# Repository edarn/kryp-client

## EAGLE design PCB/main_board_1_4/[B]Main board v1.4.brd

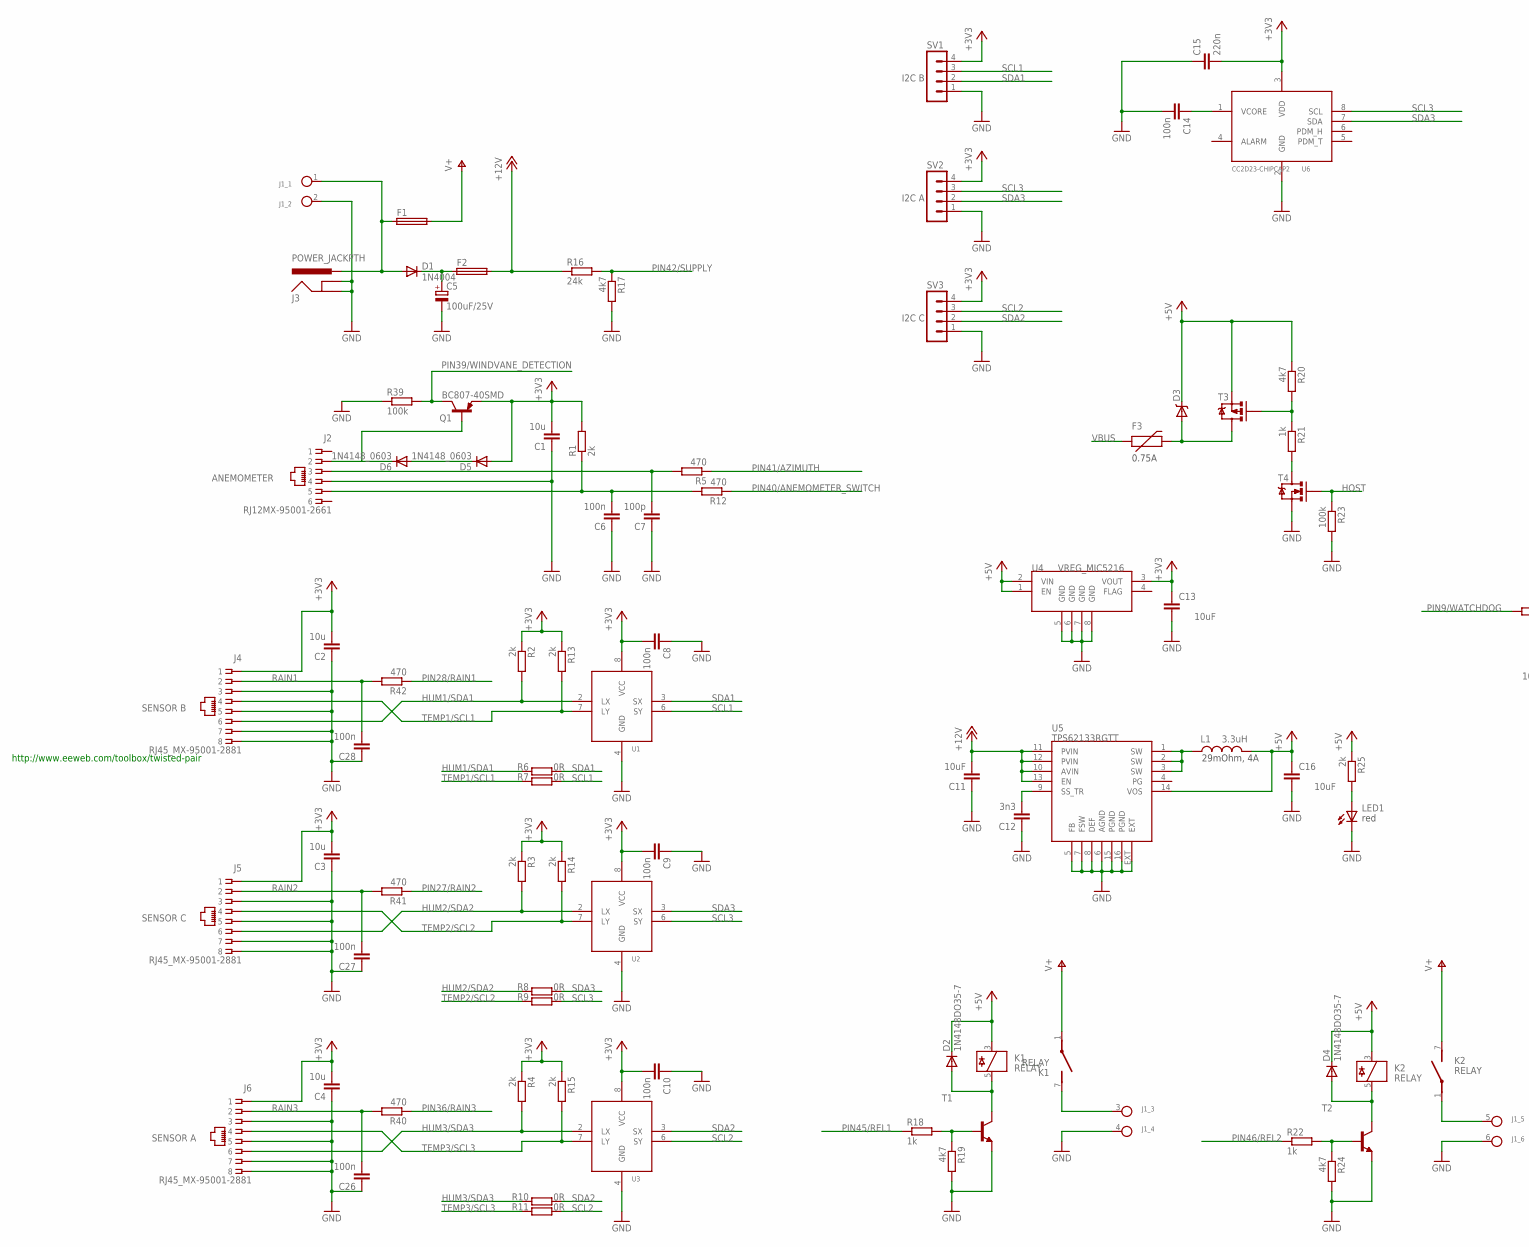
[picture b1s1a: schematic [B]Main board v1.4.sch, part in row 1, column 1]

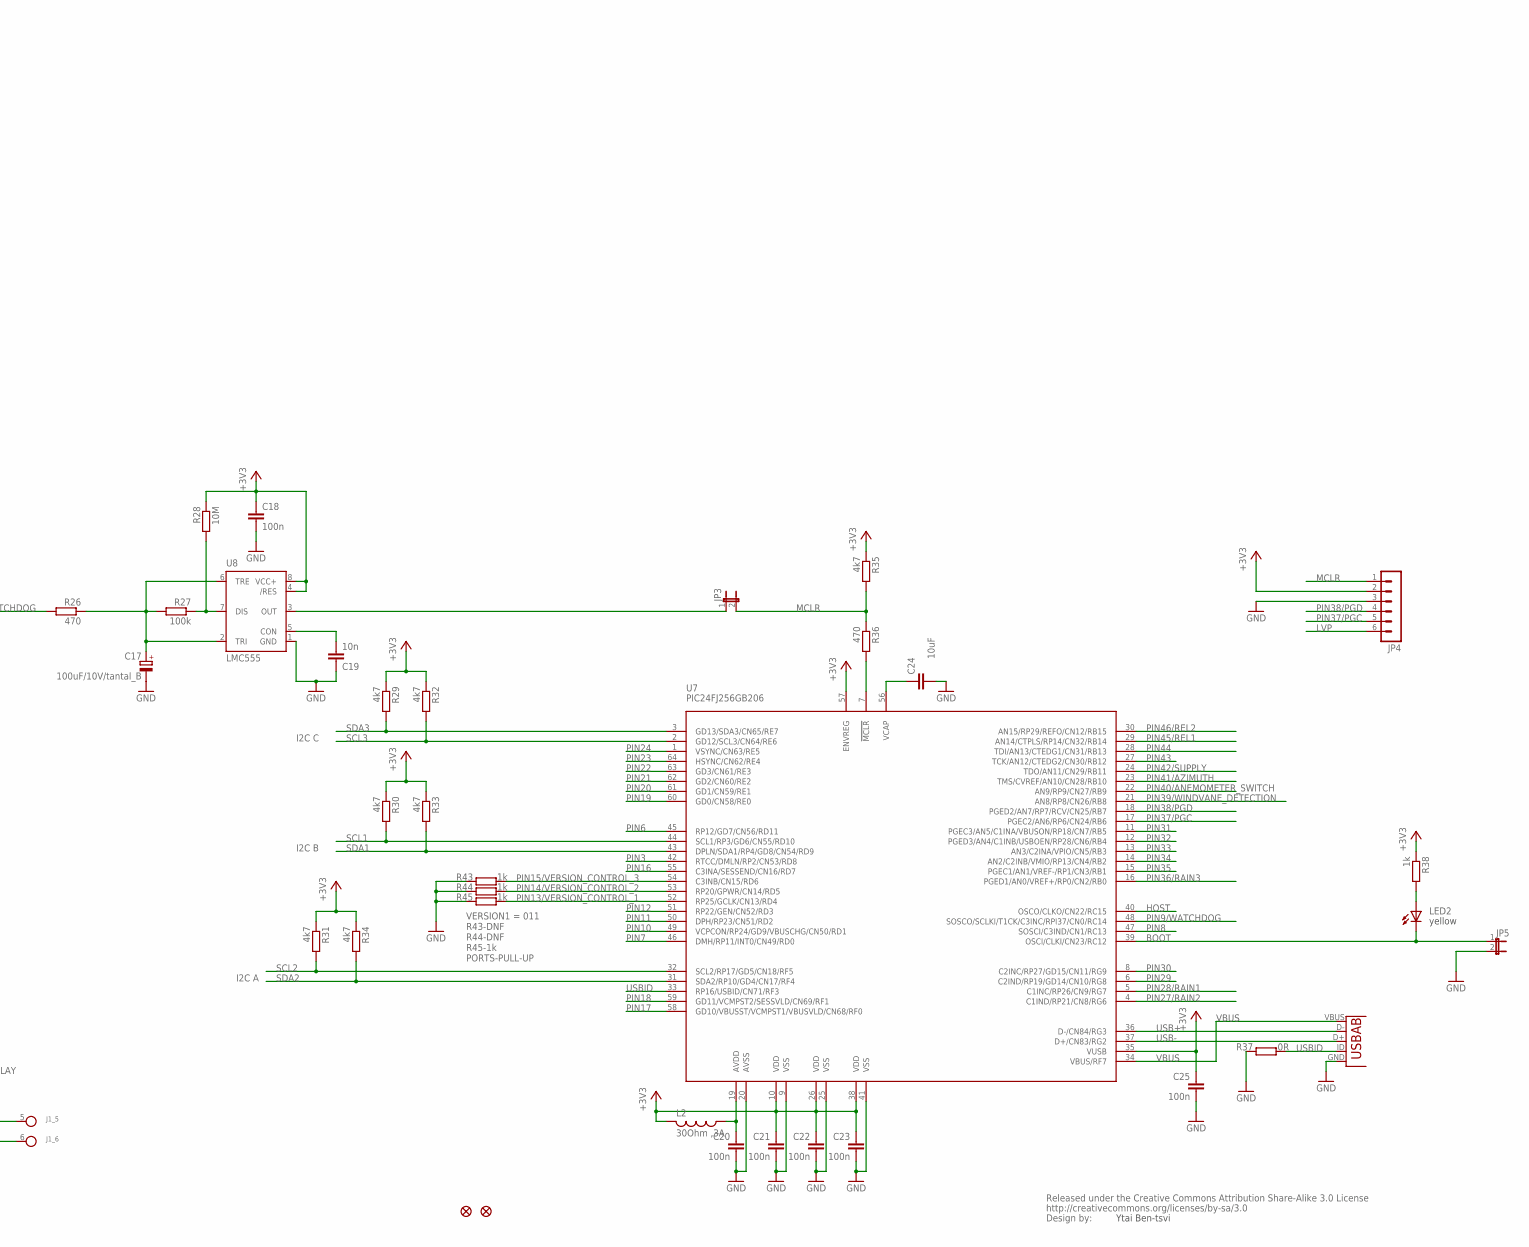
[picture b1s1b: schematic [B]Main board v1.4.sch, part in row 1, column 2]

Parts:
C1, C2, C3, C4: 10u; C1206
C5: 100uF/25V; E2-5
C6, C8, C9, C10, C14, C18, C20, C21, C22, C23, C25, C26, C27, C28: 100n; C1206
C7: 100p; C1206
C11, C13, C16, C24: 10uF; C1206
C12: 3n3; C1206
C15: 220n; C1206
C17: 100uF/10V/tantal_B; B/3528-21R
C19: 10n; C1206
D1: 1N4004; DO41-10
D2, D4: 1N4148DO35-7; DO35-7
D3: B340A; SMA-DIODE; PART# B340A
D5, D6: 1N4148_0603; D0603
F1, F2: FUSE_HOLDER; ZHL30
F3: PTCSMD; PTC-1206; PART# 0ZCA0075FF2G
J1: 6P_CONN; MOLEX_39543-0006
J2: RJ12MX-95001-2661; MX-95001-2661
J3: POWER_JACKPTH; PC-GK2.1
J4, J5, J6: RJ45_MX-95001-2881; MX-95001-2881
J7: 10104111-0001LF; USB-AB-MICRO-SMD
JP1, JP2: FIDUCIALUFIDUCIAL; MICRO-FIDUCIAL
JP3, JP5: JUMPER-2PTH; 1X02
JP4: MA06-1
K1, K2: RELAY; JV-5S-KT
L1: VLC5045T-3R3N; CR54
L2: 30Ohm ,3A; R1206
LED1: LS L29K-G1J2-1-Z; LED-1206
LED2: LY L29K-J1K2-26-Z; LED-1206
Q1: BC807-40SMD; SOT23-BEC
R1, R2, R3, R4, R13, R14, R15, R25: 2k; R1206
R5, R12, R26, R36, R40, R41, R42: 470; R1206
R6, R7, R8, R9, R10, R11, R37: 0R; R1206
R16: 24k; R1206
R17, R19, R20, R24, R29, R30, R31, R32, R33, R34, R35: 4k7; R1206
R18, R21, R22, R38, R43, R44, R45: 1k; R1206
R23, R27, R39: 100k; R1206
R28: 10M; R1206
SV1, SV2, SV3: MA04-1
T1, T2: BC817-16-NPN-SOT23-BEC; SOT23-BEC
T3: IRLML2244; SOT23-3
T4: 2N7002PW; SOT323; PART# 2N7002PW
U1, U2, U3: P82B715_I2C_BUS_EXTENDER; SO-08
U4: VREG_MIC5216; MSOP8
U5: TPS62133RGTT; QFN16-3X3MM
U6: CC2D23-CHIPCAP2
U7: PIC24FJ256GB206; PIC24FXXX_TQFP64
U8: LMC555; SO08
U$1: CREATIVE_COMMONS

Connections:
+3V3: C1.2, C2.2, C3.2, C4.2, C8.2, C9.2, C10.2, C13.2, C15.2, C18.1, C21.1, C22.1, C23.1, C25.1, D5.A, J4.1, J5.1, J6.1, JP4.2, L2.2, Q1.E, R1.2, R2.1, R3.1, R4.1, R13.1, R14.1, R15.1, R28.1, R29.1, R30.1, R31.1, R32.1, R33.1, R34.1, R35.1, R38.1, SV1.4, SV2.4, SV3.4, U1.8 (VCC), U2.8 (VCC), U3.8 (VCC), U4.3 (VOUT), U6.3 (VDD), U7.10 (VDD), U7.26 (VDD), U7.35 (VUSB), U7.38 (VDD), U7.57 (ENVREG), U8.4 (/RES), U8.8 (VCC+)
+5V: C16.2, D2.C, D3.C, D4.C, K1.3, K2.3, L1.P$2 (2), R20.1, R25.1, T3.2 (S), U4.1 (EN), U4.2 (VIN), U5.14 (VOS)
+12V: C11.2, F2.2, R16.1, U5.10 (AVIN), U5.11 (PVIN), U5.12 (PVIN), U5.13 (EN)
BOOT: JP5.1, LED2.C, U7.39 (OSCI/CLKI/CN23/RC12)
GND: C1.1, C2.1, C3.1, C4.1, C5.-, C6.1, C7.1, C8.1, C9.1, C10.1, C11.1, C12.1, C13.1, C14.2, C15.1, C16.1, C17.-, C18.2, C19.1, C20.2, C21.2, C22.2, C23.2, C24.1, C25.2, C26.1, C27.1, C28.1, J1.2, J1.4, J1.6, J2.4, J3.GND, J3.GNDBREAK, J4.3, J4.5, J4.7, J4.8, J5.3, J5.5, J5.7, J5.8, J6.3, J6.5, J6.7, J6.8, J7.GND, JP4.3, JP5.2, LED1.C, R17.2, R19.2, R23.2, R24.2, R37.2, R39.1, R43.1, R44.1, R45.1, SV1.1, SV2.1, SV3.1, T1.E, T2.E, T4.2 (S), U1.4 (GND), U2.4 (GND), U3.4 (GND), U4.5 (GND), U4.6 (GND), U4.7 (GND), U4.8 (GND), U5.5 (FB), U5.6 (AGND), U5.7 (FSW), U5.8 (DEF), U5.15 (PGND), U5.16 (PGND), U5.EXT, U6.2 (GND), U7.9 (VSS), U7.20 (AVSS), U7.25 (VSS), U7.41 (VSS), U8.1 (GND)
HOST: R23.1, T4.1 (G), U7.40 (OSCO/CLKO/CN22/RC15)
HUM1/SDA1: J4.6, R2.2, R6.2, U1.2 (LX)
HUM2/SDA2: J5.6, R3.2, R8.2, U2.2 (LX)
HUM3/SDA3: J6.6, R4.2, R10.2, U3.2 (LX)
LVP: JP4.6
MCLR: JP3.2, JP4.1, R35.2, R36.1
unnamed: D1.A, F1.1, J1.1, J3.PWR
unnamed: C6.2, J2.5, R1.1, R12.2
unnamed: C5.+, D1.C, F2.1
unnamed: C7.2, J2.3, R5.2
unnamed: C14.1, U6.1 (VCORE)
unnamed: R36.2, U7.7 (!MCLR)
unnamed: JP3.1, U8.3 (OUT)
unnamed: R18.2, R19.1, T1.B
unnamed: D2.A, K1.5, T1.C
unnamed: C19.2, U8.5 (CON)
unnamed: D6.C, J2.2, Q1.B
unnamed: J1.3, K1.7 (S)
unnamed: C17.+, R26.1, R27.2, U8.2 (TRI), U8.6 (TRE)
unnamed: D5.C, D6.A
unnamed: R27.1, R28.2, U8.7 (DIS)
unnamed: R22.2, R24.1, T2.B
unnamed: D4.A, K2.5, T2.C
unnamed: C24.2, U7.56 (VCAP)
unnamed: J1.5, K2.1
unnamed: LED2.A, R38.2
unnamed: LED1.A, R25.2
unnamed: D3.A, F3.2, T3.3 (D)
unnamed: C12.2, U5.9 (SS_TR)
unnamed: L1.P$1 (1), U5.1 (SW), U5.2 (SW), U5.3 (SW)
unnamed: C20.1, L2.1, U7.19 (AVDD)
unnamed: R20.2, R21.1, T3.1 (G)
unnamed: R21.2, T4.3 (D)
PIN3: U7.42 (RTCC/DMLN/RP2/CN53/RD8)
PIN6: U7.45 (RP12/GD7/CN56/RD11)
PIN7: U7.46 (DMH/RP11/INT0/CN49/RD0)
PIN8: U7.47 (SOSCI/C3IND/CN1/RC13)
PIN9/WATCHDOG: R26.2, U7.48 (SOSCO/SCLKI/T1CK/C3INC/RPI37/CN0/RC14)
PIN10: U7.49 (VCPCON/RP24/GD9/VBUSCHG/CN50/RD1)
PIN11: U7.50 (DPH/RP23/CN51/RD2)
PIN12: U7.51 (RP22/GEN/CN52/RD3)
PIN13/VERSION_CONTROL_1: R45.2, U7.52 (RP25/GCLK/CN13/RD4)
PIN14/VERSION_CONTROL_2: R44.2, U7.53 (RP20/GPWR/CN14/RD5)
PIN15/VERSION_CONTROL_3: R43.2, U7.54 (C3INB/CN15/RD6)
PIN16: U7.55 (C3INA/SESSEND/CN16/RD7)
PIN17: U7.58 (GD10/VBUSST/VCMPST1/VBUSVLD/CN68/RF0)
PIN18: U7.59 (GD11/VCMPST2/SESSVLD/CN69/RF1)
PIN19: U7.60 (GD0/CN58/RE0)
PIN20: U7.61 (GD1/CN59/RE1)
PIN21: U7.62 (GD2/CN60/RE2)
PIN22: U7.63 (GD3/CN61/RE3)
PIN23: U7.64 (HSYNC/CN62/RE4)
PIN24: U7.1 (VSYNC/CN63/RE5)
PIN27/RAIN2: R41.1, U7.4 (C1IND/RP21/CN8/RG6)
PIN28/RAIN1: R42.1, U7.5 (C1INC/RP26/CN9/RG7)
PIN29: U7.6 (C2IND/RP19/GD14/CN10/RG8)
PIN30: U7.8 (C2INC/RP27/GD15/CN11/RG9)
PIN31: U7.11 (PGEC3/AN5/C1INA/VBUSON/RP18/CN7/RB5)
PIN32: U7.12 (PGED3/AN4/C1INB/USBOEN/RP28/CN6/RB4)
PIN33: U7.13 (AN3/C2INA/VPIO/CN5/RB3)
PIN34: U7.14 (AN2/C2INB/VMIO/RP13/CN4/RB2)
PIN35: U7.15 (PGEC1/AN1/VREF-/RP1/CN3/RB1)
PIN36/RAIN3: R40.1, U7.16 (PGED1/AN0/VREF+/RP0/CN2/RB0)
PIN37/PGC: JP4.5, U7.17 (PGEC2/AN6/RP6/CN24/RB6)
PIN38/PGD: JP4.4, U7.18 (PGED2/AN7/RP7/RCV/CN25/RB7)
PIN39/WINDVANE_DETECTION: Q1.C, R39.2, U7.21 (AN8/RP8/CN26/RB8)
PIN40/ANEMOMETER_SWITCH: R12.1, U7.22 (AN9/RP9/CN27/RB9)
PIN41/AZIMUTH: R5.1, U7.23 (TMS/CVREF/AN10/CN28/RB10)
PIN42/SUPPLY: R16.2, R17.1, U7.24 (TDO/AN11/CN29/RB11)
PIN43: U7.27 (TCK/AN12/CTEDG2/CN30/RB12)
PIN44: U7.28 (TDI/AN13/CTEDG1/CN31/RB13)
PIN45/REL1: R18.1, U7.29 (AN14/CTPLS/RP14/CN32/RB14)
PIN46/REL2: R22.1, U7.30 (AN15/RP29/REFO/CN12/RB15)
RAIN1: C28.2, J4.2, R42.2
RAIN2: C27.2, J5.2, R41.2
RAIN3: C26.2, J6.2, R40.2
SCL1: R7.1, R30.2, SV1.3, U1.6 (SY), U7.44 (SCL1/RP3/GD6/CN55/RD10)
SCL2: R11.1, R31.2, SV3.3, U3.6 (SY), U7.32 (SCL2/RP17/GD5/CN18/RF5)
SCL3: R9.1, R32.2, SV2.3, U2.6 (SY), U6.8 (SCL), U7.2 (GD12/SCL3/CN64/RE6)
SDA1: R6.1, R33.2, SV1.2, U1.3 (SX), U7.43 (DPLN/SDA1/RP4/GD8/CN54/RD9)
SDA2: R10.1, R34.2, SV3.2, U3.3 (SX), U7.31 (SDA2/RP10/GD4/CN17/RF4)
SDA3: R8.1, R29.2, SV2.2, U2.3 (SX), U6.7 (SDA), U7.3 (GD13/SDA3/CN65/RE7)
TEMP1/SCL1: J4.4, R7.2, R13.2, U1.7 (LY)
TEMP2/SCL2: J5.4, R9.2, R14.2, U2.7 (LY)
TEMP3/SCL3: J6.4, R11.2, R15.2, U3.7 (LY)
USB+: J7.D-, U7.36 (D-/CN84/RG3)
USB-: J7.D+, U7.37 (D+/CN83/RG2)
USBID: J7.ID (USBID), R37.1, U7.33 (RP16/USBID/CN71/RF3)
V+: F1.2, K1.1, K2.7 (S)
VBUS: F3.1, J7.VBUS, U7.34 (VBUS/RF7)

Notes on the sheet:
http://www.eeweb.com/toolbox/twisted-pair
ANEMOMETER
SENSOR B
SENSOR A
SENSOR C
I2C C
I2C A
I2C B
Ytai Ben-tsvi
yellow
red
0.75A
29mOhm, 4A
VERSION1 = 011 R43-DNF R44-DNF R45-1k PORTS-PULL-UP

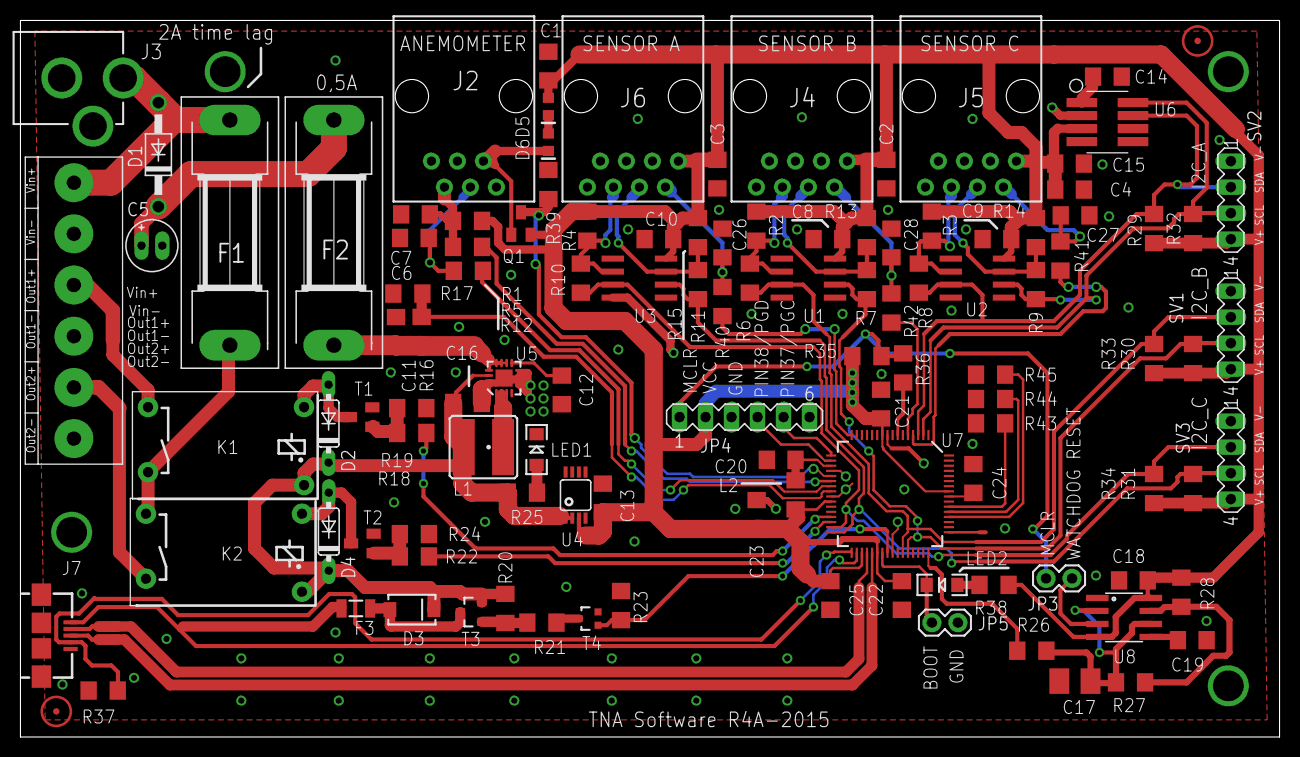
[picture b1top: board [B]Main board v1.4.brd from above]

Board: 2 copper layers, 123.0 x 70.0 mm, 117 parts (0 on the bottom side), 69 nets.

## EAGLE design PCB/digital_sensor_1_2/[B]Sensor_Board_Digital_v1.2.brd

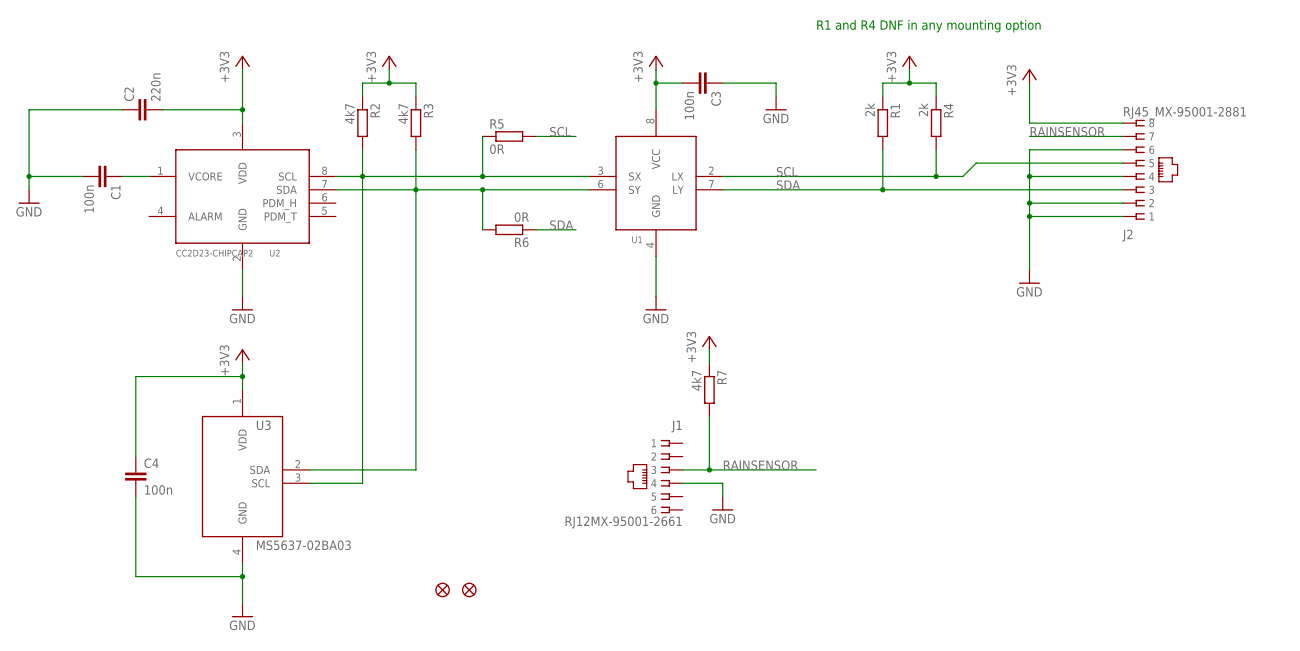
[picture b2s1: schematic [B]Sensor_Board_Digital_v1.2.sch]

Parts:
C1, C3, C4: 100n; C1206
C2: 220n; C1206
J1: RJ12MX-95001-2661; MX-95001-2661
J2: RJ45_MX-95001-2881; MX-95001-2881
JP1, JP2: FIDUCIALUFIDUCIAL; MICRO-FIDUCIAL
R1, R4: 2k; R1206
R2, R3, R7: 4k7; R1206
R5, R6: 0R; R1206
U1: P82B715_I2C_BUS_EXTENDER; SO-08
U2: CC2D23-CHIPCAP2
U3: MS5637-02BA03

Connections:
+3V3: C2.2, C3.2, C4.1, J2.8, R1.1, R2.1, R3.1, R4.1, R7.1, U1.8 (VCC), U2.3 (VDD), U3.1 (VDD)
GND: C1.2, C2.1, C3.1, C4.2, J1.4, J2.1, J2.2, J2.4, J2.6, U1.4 (GND), U2.2 (GND), U3.4 (GND)
unnamed: C1.1, U2.1 (VCORE)
unnamed: R2.2, R5.1, U1.3 (SX), U2.8 (SCL), U3.3 (SCL)
unnamed: R3.2, R6.2, U1.6 (SY), U2.7 (SDA), U3.2 (SDA)
RAINSENSOR: J1.3, J2.7, R7.2
SCL: J2.5, R4.2, R5.2, U1.2 (LX)
SDA: J2.3, R1.2, R6.1, U1.7 (LY)

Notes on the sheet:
R1 and R4 DNF in any mounting option

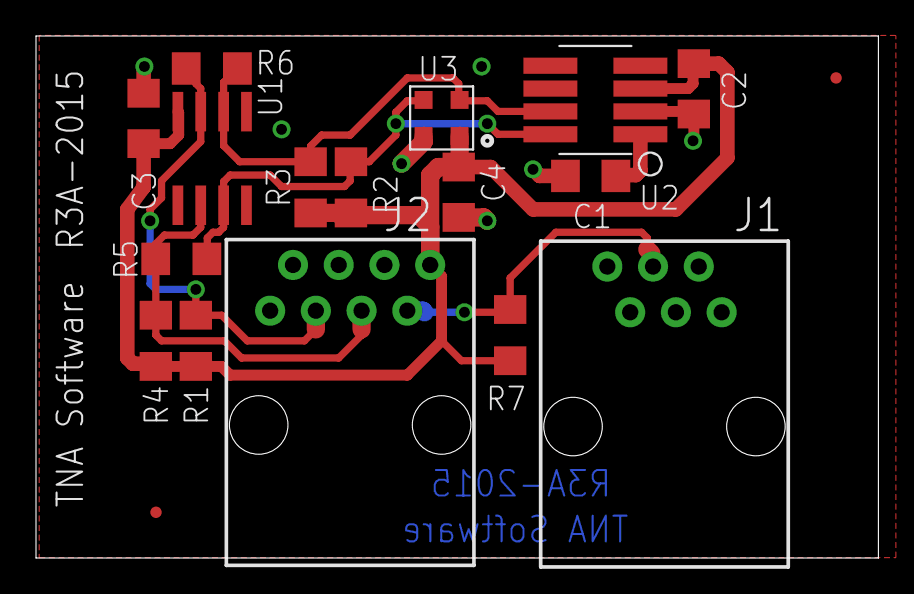
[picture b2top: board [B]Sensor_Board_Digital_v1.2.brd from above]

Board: 2 copper layers, 46.8 x 29.0 mm, 18 parts (0 on the bottom side), 8 nets.

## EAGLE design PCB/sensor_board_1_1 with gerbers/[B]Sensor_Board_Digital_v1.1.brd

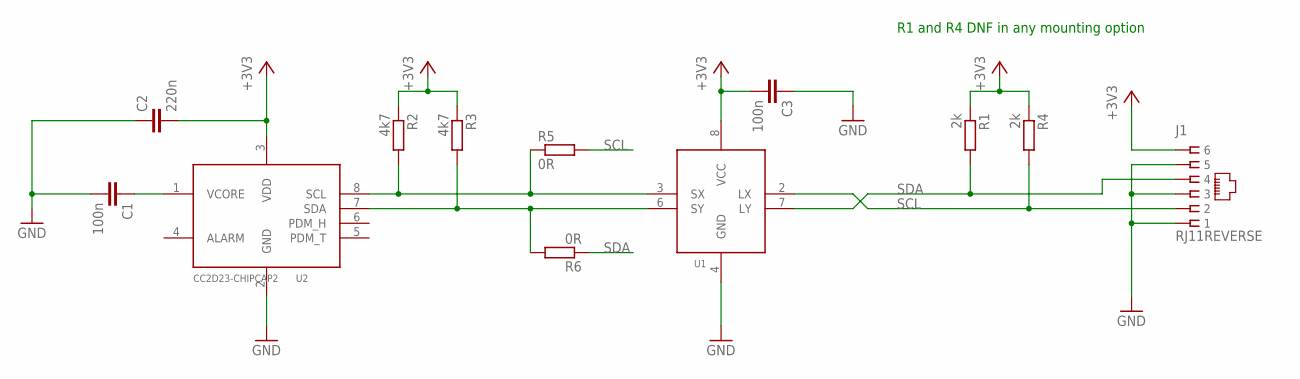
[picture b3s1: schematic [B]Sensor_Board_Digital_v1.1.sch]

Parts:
C1, C3: 100n; C1206
C2: 220n; C1206
J1: RJ11REVERSE; MX-95001-2661
R1, R4: 2k; R1206
R2, R3: 4k7; R1206
R5, R6: 0R; R1206
U1: P82B715_I2C_BUS_EXTENDER; SO-08
U2: CC2D23-CHIPCAP2

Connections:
+3V3: C2.2, C3.2, J1.6, R1.1, R2.1, R3.1, R4.1, U1.8 (VCC), U2.3 (VDD)
GND: C1.2, C2.1, C3.1, J1.1, J1.3, J1.5, U1.4 (GND), U2.2 (GND)
unnamed: C1.1, U2.1 (VCORE)
unnamed: R2.2, R5.1, U1.3 (SX), U2.8 (SCL)
unnamed: R3.2, R6.2, U1.6 (SY), U2.7 (SDA)
SCL: J1.2, R4.2, R5.2, U1.2 (LX)
SDA: J1.4, R1.2, R6.1, U1.7 (LY)

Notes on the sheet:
R1 and R4 DNF in any mounting option

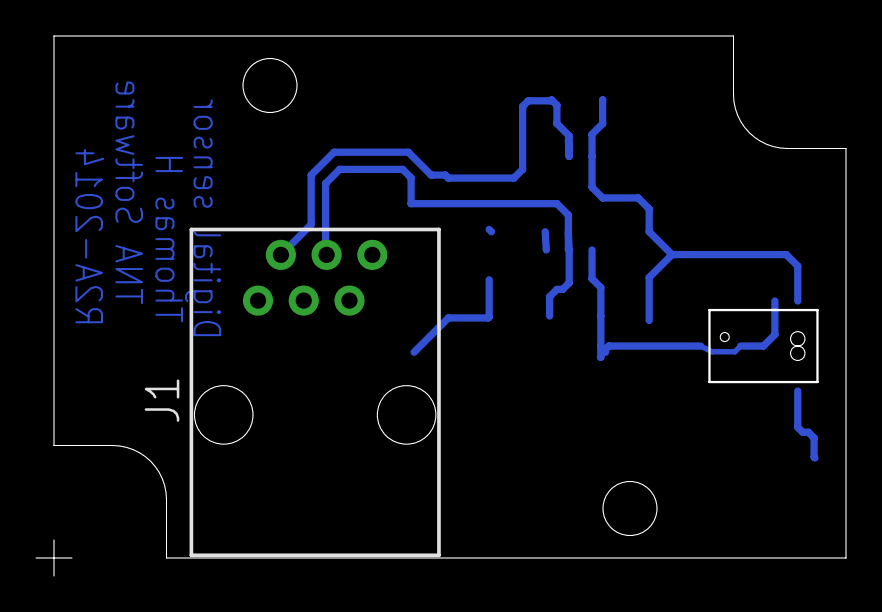
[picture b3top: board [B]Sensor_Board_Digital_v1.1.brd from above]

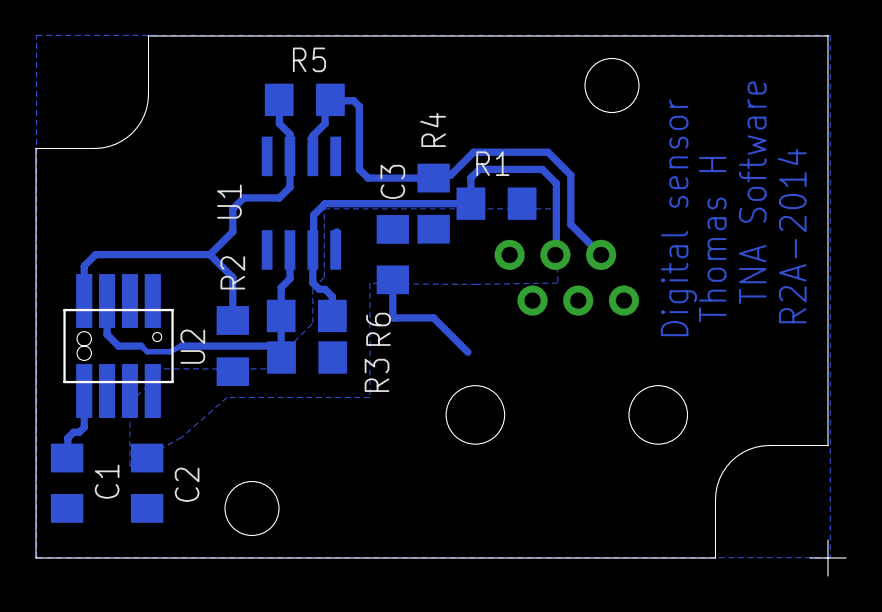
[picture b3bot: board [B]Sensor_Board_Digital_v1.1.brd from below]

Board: 2 copper layers, 45.0 x 30.0 mm, 12 parts (11 on the bottom side), 7 nets.

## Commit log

2013-09-01 Initial upload
2013-09-02 changed names and cleanup
2013-09-08 removed obsolete files after renaming project
2013-10-01 Removing redundant files and removing project files
2013-10-01 Renamed GUI file
2013-10-03 Updated IOIO library.
2013-10-07 Fixing project properties
2013-10-07 Fixed bug when sending data to server.
2013-10-16 A more failsafe client
2013-10-31 Adding support for Surfvind and many more things
2013-11-08 Fix null check in Helper.Destroy
2013-11-10 Changes to get Surfvind to work for longer time
2013-11-10 Updated IOIO lib to latest version on github
2013-12-15 battery and temp reading and other stuff
2013-12-17 Adding a new GetFrequency method - AnalogInput
2013-12-17 modified time, added temp and battery
2013-12-17 bugfix
2013-12-19 New and modified IOIOLib - pwm changes
2013-12-19 Adding ioio test project
2013-12-27 modification to ioio lib
2013-12-31 Refactoring and temporary removing outdoor sensor
2014-01-07 Adding SetupActivity
2014-01-10 Launching Setup from optionsmenu
2014-01-10 Sorting of data to remove incorrect readings
2014-01-13 SetupActivity improvements
2014-01-13 Updated to IOIO lib version 5.0
2014-01-21 I2C Sensor
2014-01-21 Updated to IOIO Lib v5.1
2014-01-21 upates to use different sensors
2014-01-21 Two working sensors
2014-01-23 Test to cyclic restart connection to IOIO
2014-01-26 Enhancing setup and refactor
2014-01-28 Bugfix - update name and position from Setup
2014-02-04 Cleanup and fix setup
2014-02-19 Modified UI Removed Debugger Activity Temporary commented away all Surfvind code in service Added support for Starting/Stopping fan for new circuits.
2014-02-21 Fan working
2014-02-21 lib files preferences
2014-03-18 Error handling when sending data
2014-07-30 Cleaned up Send function
2014-07-30 Helper only opens the used pins
2014-07-30 Lots of changes.
2014-07-31 Multiple fixes
    Catching all uncaught exceptions.
    Added logging to file.
    Refactored and cleaned up.
2014-08-01 Renamed folder and Project
2014-08-01 Improved Setup and Runtime of Service
2014-09-21 Who knows what fixes this is. :)
2014-10-15 Addin new ui parts for weather station
2014-10-17 Project restructure
    Adding Web project VindInfo and Surfvind.
    Adding support for Gradle/Android Studio.
2014-10-25 updating .gitignore
2014-10-25 lots of build files beeing removed.
2014-10-25 Modifying the GUI.
2014-10-26 fix builderrors
2014-10-29 Minor ui changes
2014-10-29 Adding standalone android client for Surfvind web page
2014-10-29 Restructuring project again
2014-10-29 fix some crap
2015-01-03 Updatig dte format in log and UI
2015-01-10 Fixing timestamp to reflect TimeZone and DayLight saving.
2015-01-11 Adding new files previously only located on server. :)
2015-01-11 Converting Surfvind Web project to Visual Studio Express 2013
2015-01-11 Refactoring and optimizing
    Cleaning up GenGraphs and Default
2015-01-11 Updating gitignore
2015-01-11 gitIgnore
2015-01-15 Refactoring and optimizing old crappy code. :-)
2015-01-15 Ignore
2015-01-16 Fixed sql connection problem and reformatted code.
2015-01-17 Fix calculation error in temperature!!
2015-01-17 Fixing project file and stepping down min sdk level.
2015-01-17 Reformatting and possible bugfix. Who knows. :-)
2015-01-19 Upgrade to latest Android studio
2015-01-28 Adding CrawlSpace images
2015-01-28 testing rotate of sensor pointers
2015-01-28 Cleanup some and add basic support for humidity sensor in SurfVind
2015-01-28 Adding PCB with watchdog, Gerbers and BOM. Revision 2 of BOM was sent to china for manufacturing.
2015-01-28 Adding BT support again.
2015-02-06 update watchdog and add measurment if temp/moisture works
2015-02-06 Update UI for WeatherStation.
2015-02-06 Updated UI
2015-02-06 Adding icons to Surfvind.
2015-02-06 .gitignore
2015-02-06 minor ui stuff
2015-02-06 Adding ioio-binaries
2015-02-06 Image optimizations
2015-02-06 Sending humidity and tempterature to online database for Surfvind.
2015-02-06 Better (?) background for compass
2015-02-11 Adding power, temp and humidity to Surfvind.se
2015-03-10 Blandat
2015-03-11 Updates according to the new R3A board from China
2015-06-03 Refactoring alot.
    Lots of changes, unstable
2015-06-03 Changes for the Websites
2015-06-07 Bugfix - SurfvindStats getAverage function did not average all parameters.
2015-07-10 Correction of temperature
    Also layout change and adding default name to sensor if none is
    provided.
2015-07-10 layoutfixes and setupguide
2015-07-12 Cleanup of Helper, and moving some files.
2015-07-15 Adding message to show that a sensor is not connected.
2015-07-21 Dokument
2015-07-21 Fuktsensor 1.2
2015-07-23 Adding 3d models
2015-07-27 Adding new WeatherMaster Icon
2015-07-28 Lagt till manual och stegat versionsnr
2015-07-28 dokumentändring.
2015-07-28 Update ioio libs to latest from master
2015-07-28 Shortening the restart servcie watchdog to 10 sec instead om 10 minutes.
    Making sure "0" is returned when no valid data is returned from sensors.
2015-08-08 Google Analytics and bugfixes
    Analytics and ui bugfixes
2015-08-08 version change
2015-08-09 New release
2015-08-12 updated lots of gradle files to get it to run on new computer.
2015-08-13 Only generate all diagrams if no imei was sent at all.
2015-08-13 Vindinfo should only show the active sensors, not all.
    NOT TESTED
2015-08-28 Updating documents
2015-08-28 removing .suo files from versioncontrol
2015-08-28 Surfvind.suo deleted
2015-08-28 Temperature and updates to generation of compass and speed image
2015-08-28 deleting Vindinfo.suo
2015-08-28 Removing more crap files from project (Surfvinds bin folder)
2015-08-28 deleting files
2015-08-28 autoformat and some minor crap
2015-09-11 3d model changes
2015-09-15 Making holes bigger in box
2015-09-15 Just an example RestService added
2015-09-15 Adding sensorPCB and some other small stuff
2015-09-16 Removing redundant files....again! :-)
2015-09-21 Android Project files updated.
    Gson included
    Test files removed
2015-09-21 Layoutchanges
    Removing Title bar
    Restructuring Setup
2015-09-29 Many changes to SurfvindWeb.
    RestService created to make .php files redundant. - Not tested fully
    Removed .user files etc and updated .gitignore with lots of VisualStudio related user files.
    Created a ViewCrawlspace, also to remove .php files
    Updated documents.
    Added new version of PCB, not final
2015-09-29 Updated common logger service to use the new RestService in visual studio. Not tested as server is not deployed yet.
    Also added support for tracking events from new crawlspacemonitor app
2015-09-29 Adding new crawlspacemonitor app.
2015-10-07 Dokumentationsändringar
2015-10-29 RestService changes and more. :)
2015-10-29 Documentation
2015-11-01 Service updates.
2015-11-06 Various changes
    Adding new docs
    Removing Applet
    Removing lots of usings..
    Publish not working directly to ftp. publish to filesystem first instead
2016-04-13 Uppdaterat firmware till korten
2016-05-03 Latest revision of PCB with support for RainGauge and some other sensors.
2016-05-03 Forgot BOM for sensor card
2016-05-16 PCB detaljer
2016-05-16 Okända Surfvind Web ändringar
2016-05-16 Reklam till väderbitna
2016-05-16 Removing dependencies to local ioio libs, now using gradle imports instead
2016-05-16 Removing call to Restart in ioio as this does not exist in the official libs
2016-05-16 Added support to find out which version of the PCB we are connected to
2016-06-10 Added support to obtain Barometric preassure and rain from new sensors.
2016-06-10 Rough support to send air preassure and rainpulses to backend.
2016-06-13 Update with UI support for rain and airpreassure
2016-06-15 gradle updates, target sdk updates - This commit does not build
2016-06-19 Updated gradle files to use sdk 24
2016-06-19 Fixed layout for new sensors
2016-06-19 initial changes - more needed to replace HttpClient
2016-06-20 Updated setup activity to use OKHttpClient
2016-07-18 Multidex support when using librarys with more than 64K methods.
2016-07-21 Updated layout for CrawlSpace Monitor
2016-08-09 Updating so that crawlspacemonitor api adds data to db
2016-08-09 Fixing setup and some minor bugs for crawlspacemonitor
2016-08-09 Fixing setup and some minor bugs for crawlspacemonitor v2
2016-08-10 Vindinfo now displays AirPressure and Rainfall from database (only visible if != 0)
2016-08-10 Adding some support for AirPressure and RainFall to Surfvind RestService.
2016-08-10 more changes
2016-08-10 Bugfix - rename parameter timeStamp to time
2016-08-12 Various changes both for Crawlspace, Surfvind and Common Logger
2016-08-12 chart stuff
2016-08-12 fix sql problem
2016-08-12 Krypgrund and Surfvind app changes
2016-08-12 Release to Google Play for both apps.
2016-08-12 Adding support for obtaining the latest data only and also fetching all stations
2016-08-12 Various
2016-08-14 Adding firebase analytics, Fixing setupActivity - radiobuttons and background
2016-08-14 Lots of small fixes, also added analytics to Crawlspace
2016-08-14 Trying to fix the updatelocation script
2016-08-15 Various changes
2016-08-18 Firebase in some webpages
2016-08-18 Rain bugfix
2016-08-18 Interface for obtaining rainfall
2016-08-20 AirPressure and rain support for Surfvind

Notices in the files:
parts and their libraries:
SparkFun: Licensing: CC v3.0 Share-Alike You are welcome to use this library for commercial purposes.
SparkFun-Aesthetics: Released under the Creative Commons Attribution Share-Alike 3.0 License
SparkFun-Aesthetics: http://creativecommons.org/licenses/by-sa/3.0
